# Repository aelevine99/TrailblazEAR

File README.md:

# TrailblazEAR
 A visual aid for detecting sirens while driving

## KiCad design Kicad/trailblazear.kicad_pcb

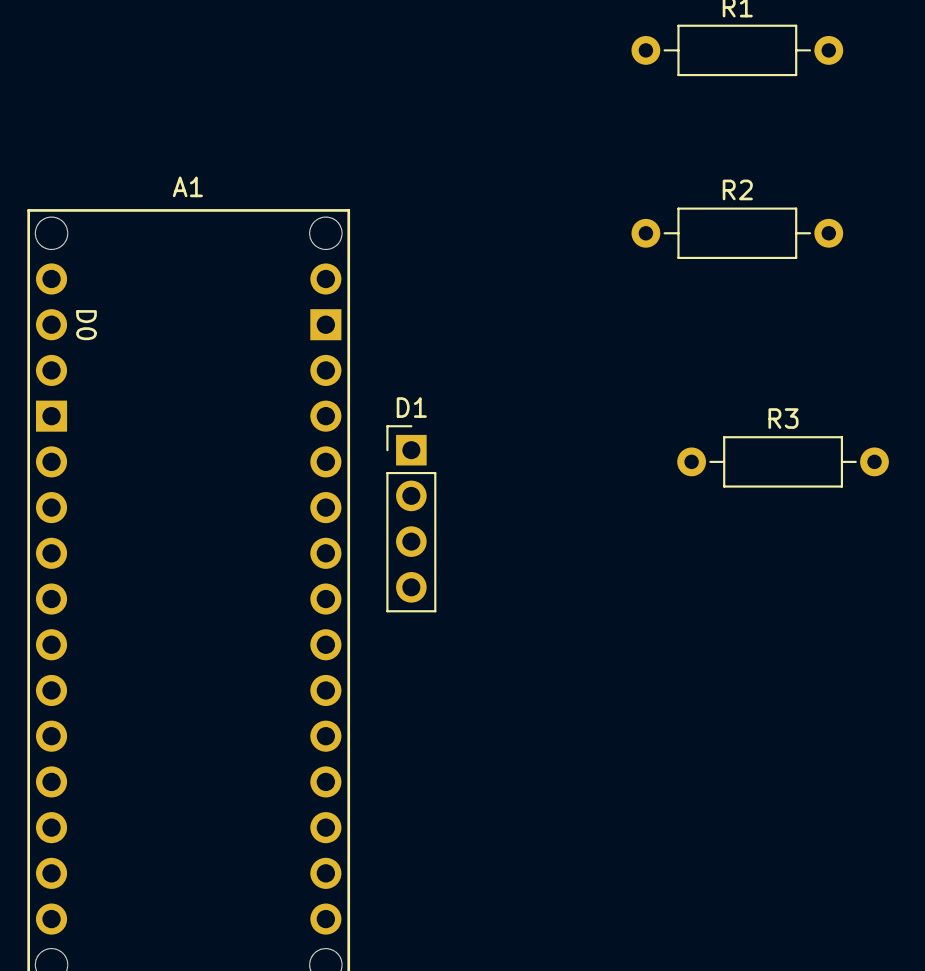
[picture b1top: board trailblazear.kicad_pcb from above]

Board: 2 copper layers, 5 parts (0 on the bottom side), 4 nets, no tracks yet.

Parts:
A1: Arduino_Nano_33_BLE_Socket; Arduino_Nano_Every_Socket
D1: NeoPixel_THT; PinHeader_1x04_P2.54mm_Vertical
R1, R2: 5.1kΩ; R_Axial_DIN0207_L6.3mm_D2.5mm_P10.16mm_Horizontal
R3: 470Ω; R_Axial_DIN0207_L6.3mm_D2.5mm_P10.16mm_Horizontal

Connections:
GND: A1.GND2 (GND), D1.2 (GND), R1.1 (+), R2.1 (+)
unnamed: D1.4 (DIN), R3.1 (+)
unnamed: A1.D4, R3.2 (-)
VBUS: A1.VIN, D1.3 (VDD)

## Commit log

2024-01-23 schematic
2024-02-05 IDE setup
2024-02-05 folder renaming
